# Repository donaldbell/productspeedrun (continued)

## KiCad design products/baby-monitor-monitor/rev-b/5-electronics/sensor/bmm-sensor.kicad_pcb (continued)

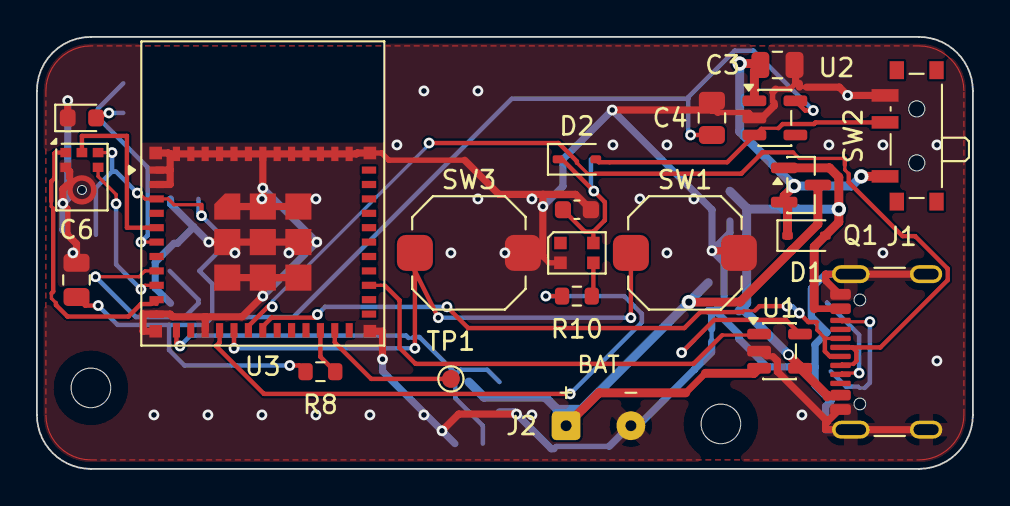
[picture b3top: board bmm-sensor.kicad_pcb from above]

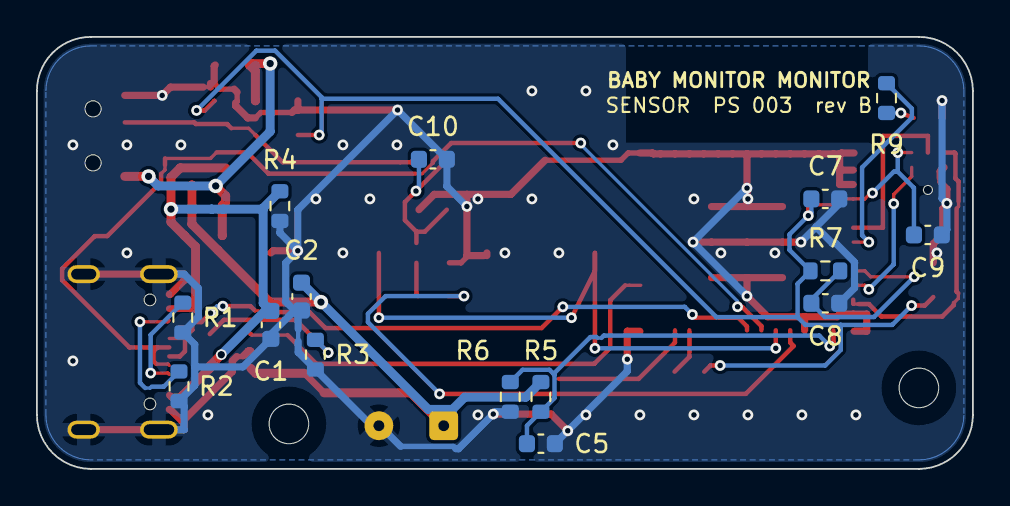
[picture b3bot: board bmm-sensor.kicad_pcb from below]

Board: 2 copper layers, 52.0 x 24.0 mm, 38 parts (15 on the bottom side), 25 nets.

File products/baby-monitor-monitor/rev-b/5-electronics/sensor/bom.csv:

Ref,Qty,Value,Description,Footprint,MPN
C1 C2,2,4.7uF,"Capacitor, ceramic, 4.7 uF 16 V X5R 0603",C_0603_1608Metric,CL10A475KO8NNNC
C3 C4 C6,3,10uF,"Capacitor, ceramic, 10 uF 25 V X5R 0805",C_0805_2012Metric,CL21A106KAYNNNE
C5 C7 C9 C11,4,100nF,"Capacitor, ceramic, 100 nF 50 V X7R 0603",C_0603_1608Metric,CC0603KRX7R9BB104
C8 C10,2,1uF,"Capacitor, ceramic, 1 uF 50 V X5R 0603",C_0603_1608Metric,CL10A105KB8NNNC
D1 D2,2,1N5819WS,Schottky 40 V 1 A SOD-323: USB into the system rail,D_SOD-323,1N5819WS
J1,1,USB-C,"USB-C receptacle, USB 2.0, 16 pin, top mount: power, charging and flashing (ESP32-C6 native USB)",USB_C_Receptacle_GCT_USB4105-xx-A_16P_TopMnt_Horizontal,USB4105-GF-A
LED1,1,green,LED green 0603: status under the front light pipe,LED_0603_1608Metric,KT-0603G
LED2,1,WS2812B-2020,RGB LED 2 x 2 mm under the clear snooze bar: location in the dark + state,LED_WS2812B-2020_PLCC4_2.0x2.0mm,WS2812B-2020
Q1,1,AO3401A,P-MOSFET -30 V -4 A SOT-23: battery into the system rail when USB is absent,SOT-23,AO3401A
R1 R2,2,5.1k,"Resistor, 1 %, 0603, 5.1k",R_0603_1608Metric,0603WAF5101T5E
R3,1,3.9k,"Resistor, 1 %, 0603, 3.9k",R_0603_1608Metric,0603WAF3901T5E
R4,1,100k,"Resistor, 1 %, 0603, 100k",R_0603_1608Metric,0603WAF1003T5E
R5 R6,2,1M,"Resistor, 1 %, 0603, 1M",R_0603_1608Metric,0603WAF1004T5E
R7 R8,2,10k,"Resistor, 1 %, 0603, 10k",R_0603_1608Metric,0603WAF1002T5E
R9,1,1k,"Resistor, 1 %, 0603, 1k",R_0603_1608Metric,0603WAF1001T5E
R10,1,100,"Resistor, 1 %, 0603, 100",R_0603_1608Metric,0603WAF1000T5E
SW1 SW3,2,I'M AWAKE,"Tact switch 6 x 6 x 5 mm SMD under the snooze bar's back end: tap = I'm awake, hold = test / pair",SW_Push_1TS009xxxx-xxxx-xxxx_6x6x5mm,1TS009A-1800-5000-CT
SW2,1,POWER,"Slide switch SPDT right-angle SMD (C&K PCM12): on = LDO enabled, off = EN to GND",SW_SPDT_PCM12,PCM12SMTR
U1,1,MCP73831T-2ACI/OT,"Li-ion/LiPo linear charger 4.2 V, SOT-23-5",SOT-23-5,MCP73831T-2ACI/OT
U2,1,AP2112K-3.3TRG1,"LDO 3.3 V 600 mA, SOT-23-5, enabled by the power switch",SOT-23-5,AP2112K-3.3TRG1
U3,1,ESP32-C6-MINI-1-N4,"ESP32-C6 Wi-Fi 6 / BLE 5 / 802.15.4 module (ESP-NOW), 4 MB flash, PCB antenna, 13.2 x 16.6 x 2.4 mm",ESP32-C6-MINI-1,ESP32-C6-MINI-1-N4
U4,1,ICS-43434,"I2S MEMS microphone, bottom port over a 1 mm hole through the board, L/R low = left slot",InvenSense_ICS-43434-6_3.5x2.65mm,ICS-43434
BT1,1,LiPo 2000 mAh,"LiPo 3.7 V ~2000 mAh with protection PCB, 103450 (10 x 34 x 50 mm), leads soldered to J2",off-board,generic 103450

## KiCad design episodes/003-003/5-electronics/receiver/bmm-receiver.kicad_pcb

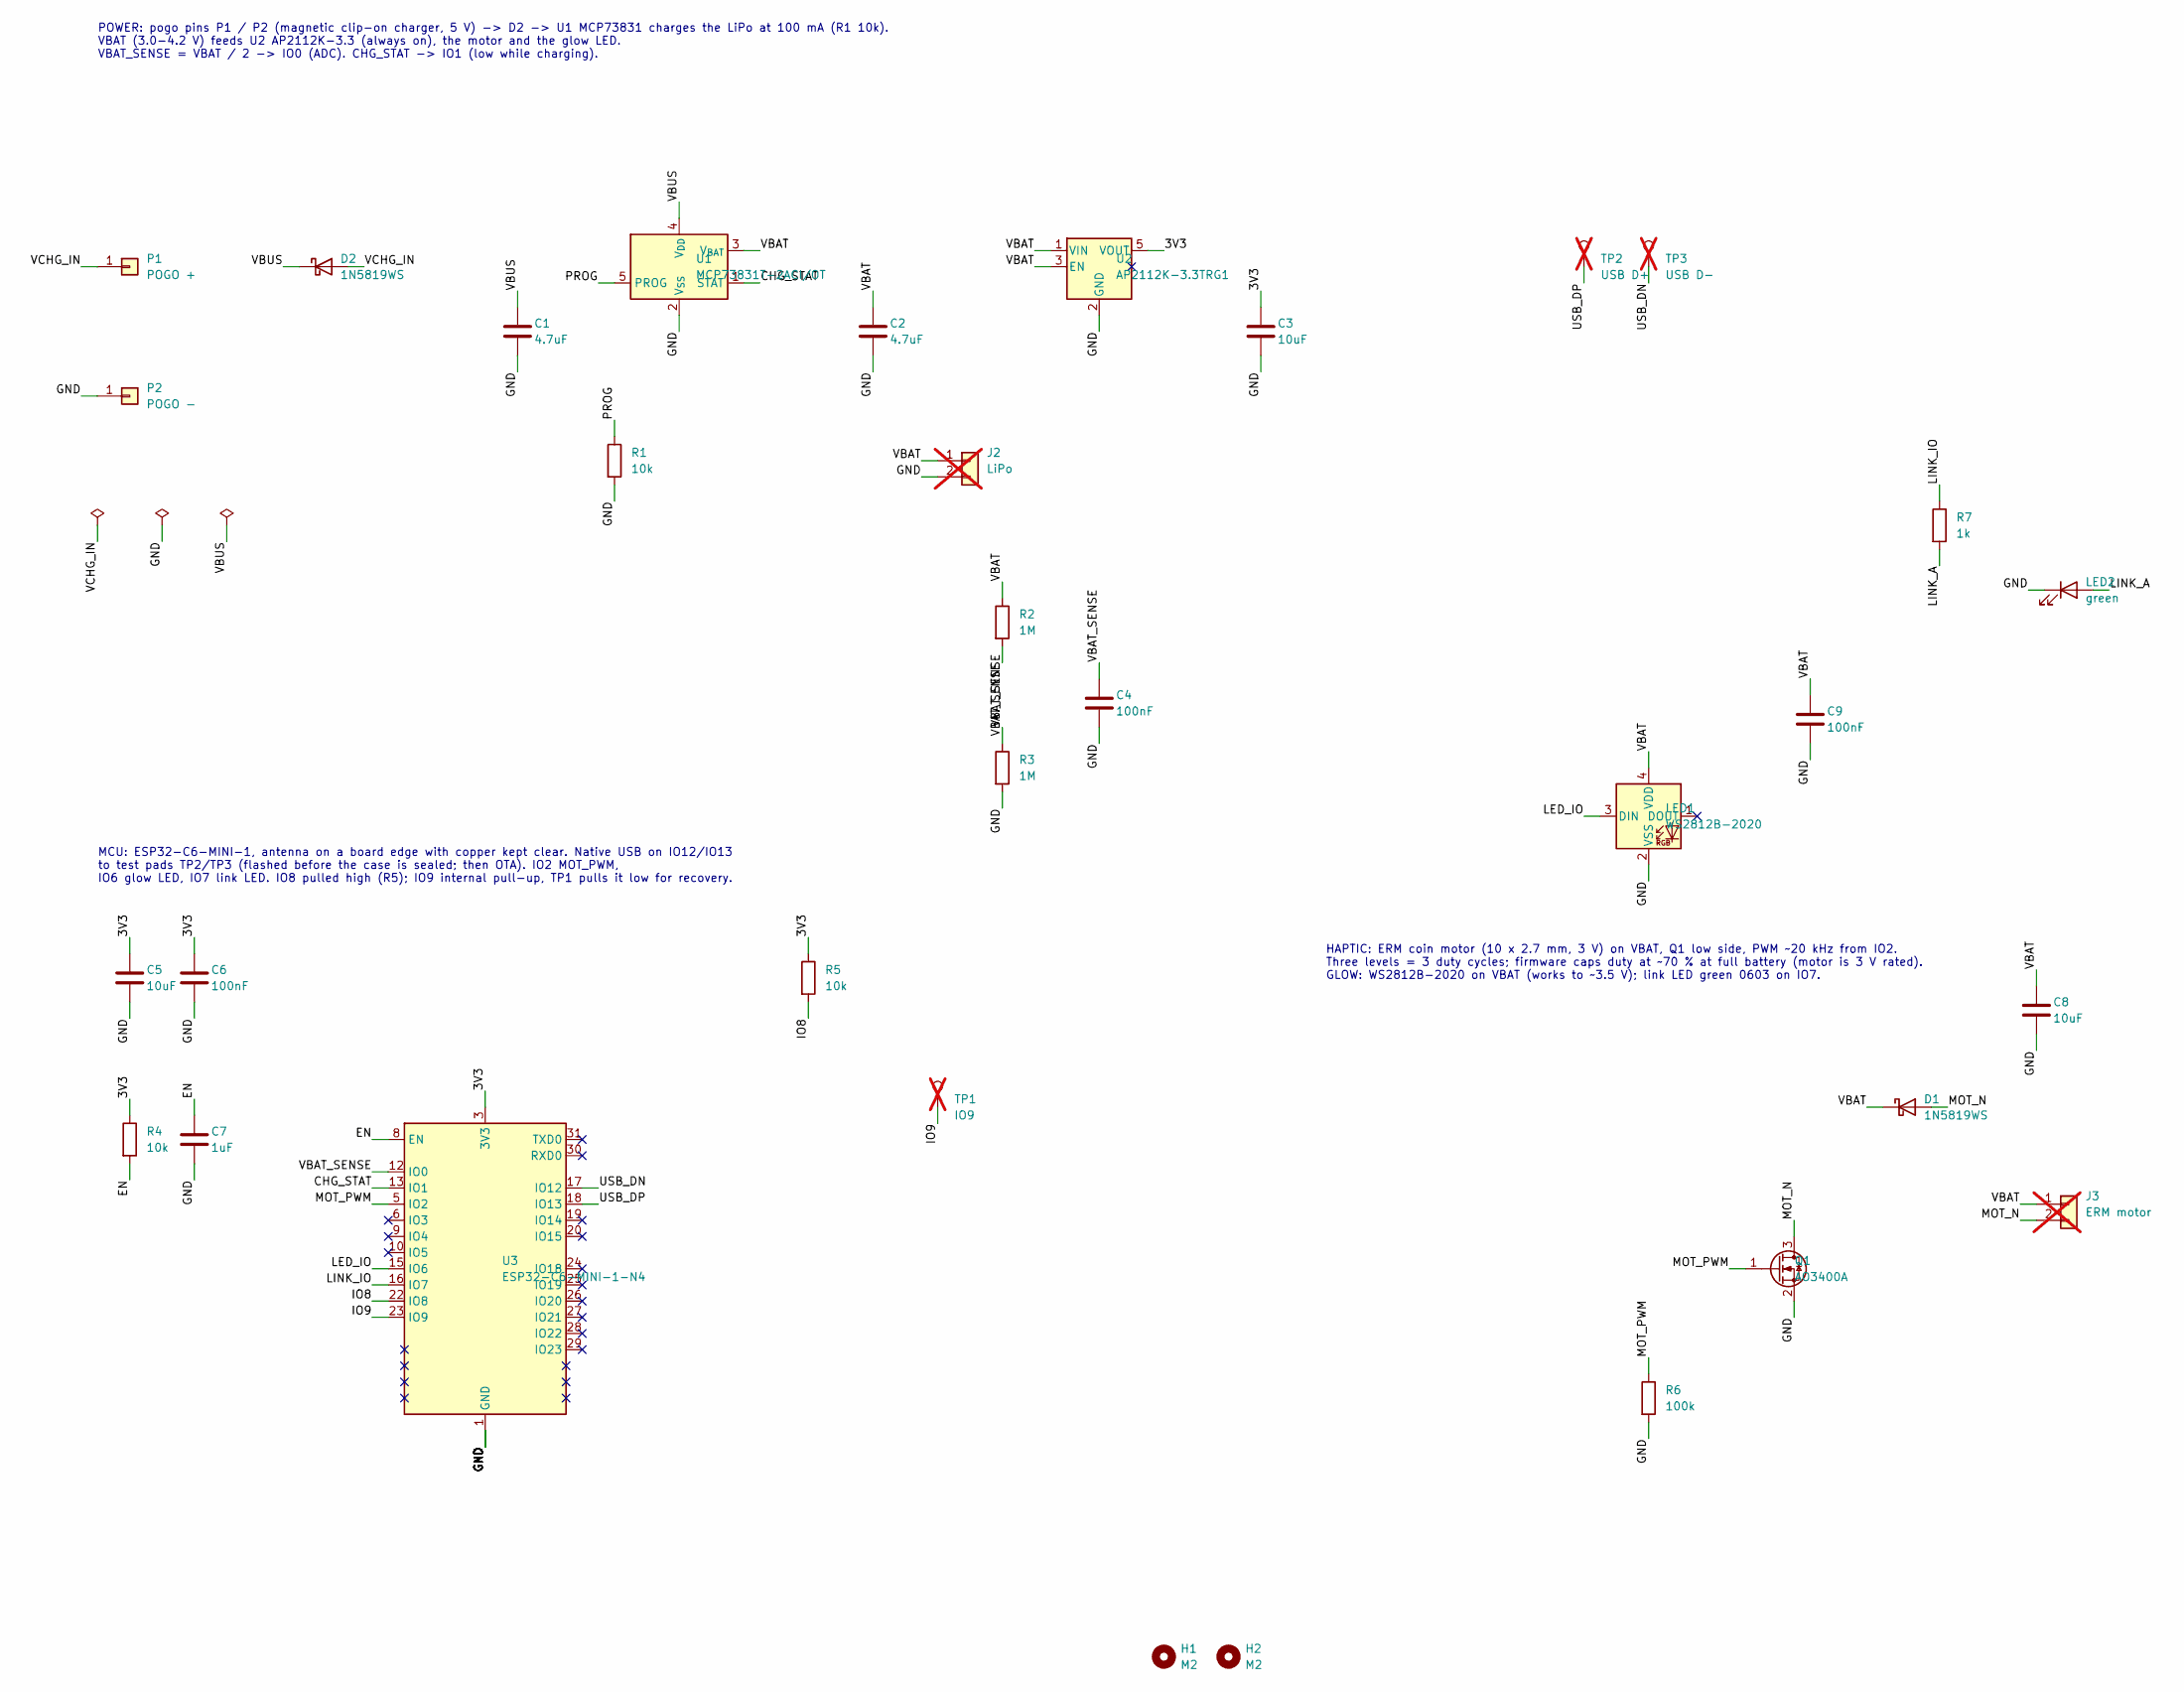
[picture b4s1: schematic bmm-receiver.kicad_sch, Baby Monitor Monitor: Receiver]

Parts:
C1, C2: 4.7uF; C_0603_1608Metric; MPN CL10A475KO8NNNC; LCSC C19666
C3, C5, C8: 10uF; C_0805_2012Metric; MPN CL21A106KAYNNNE; LCSC C15850
C4, C6, C9: 100nF; C_0603_1608Metric; MPN CC0603KRX7R9BB104; LCSC C14663
C7: 1uF; C_0603_1608Metric; MPN CL10A105KB8NNNC; LCSC C15849
D1, D2: 1N5819WS; D_SOD-323; MPN 1N5819WS; LCSC C191023
H1, H2: M2; MountingHole_2.2mm_M2
J2: LiPo; SolderWire-0.1sqmm_1x02_P3.6mm_D0.4mm_OD1mm; not fitted
J3: ERM motor; SolderWire-0.1sqmm_1x02_P3.6mm_D0.4mm_OD1mm; not fitted
LED1: WS2812B-2020; LED_WS2812B-2020_PLCC4_2.0x2.0mm; MPN WS2812B-2020; LCSC C965555
LED2: green; LED_0603_1608Metric; MPN KT-0603G; LCSC C72043
P1: POGO +; TestPoint_Pad_D2.0mm; MPN Mill-Max 0907 SMD spring pin (~5 mm)
P2: POGO -; TestPoint_Pad_D2.0mm; MPN Mill-Max 0907 SMD spring pin (~5 mm)
Q1: AO3400A; SOT-23; MPN AO3400A; LCSC C20917
R1, R4, R5: 10k; R_0603_1608Metric; MPN 0603WAF1002T5E; LCSC C25804
R2, R3: 1M; R_0603_1608Metric; MPN 0603WAF1004T5E; LCSC C22935
R6: 100k; R_0603_1608Metric; MPN 0603WAF1003T5E; LCSC C25803
R7: 1k; R_0603_1608Metric; MPN 0603WAF1001T5E; LCSC C21190
TP1: IO9; TestPoint_Pad_D1.0mm; not fitted
TP2: USB D+; TestPoint_Pad_D1.0mm; not fitted
TP3: USB D-; TestPoint_Pad_D1.0mm; not fitted
U1: MCP73831T-2ACI/OT; SOT-23-5; MPN MCP73831T-2ACI/OT; LCSC C424093
U2: AP2112K-3.3TRG1; SOT-23-5; MPN AP2112K-3.3TRG1; LCSC C51118
U3: ESP32-C6-MINI-1-N4; ESP32-C6-MINI-1; MPN ESP32-C6-MINI-1-N4

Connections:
/3V3: C3.1, C5.1, C6.1, R4.1, R5.1, U2.5 (VOUT), U3.3 (3V3)
/CHG_STAT: U1.1 (STAT), U3.13 (IO1)
/EN: C7.1, R4.2, U3.8 (EN)
/GND: C1.2, C2.2, C3.2, C4.2, C5.2, C6.2, C7.2, C8.2, C9.2, J2.2, LED1.2 (VSS), LED2.1 (K), P2.1, Q1.2 (S), R1.2, R3.2, R6.2, U1.2 (V_{SS}), U2.2 (GND), U3.1 (GND), U3.2 (GND), U3.11 (GND), U3.14 (GND), U3.36 (GND), U3.37 (GND), U3.38 (GND), U3.39 (GND), U3.40 (GND), U3.41 (GND), U3.42 (GND), U3.43 (GND), U3.44 (GND), U3.45 (GND), U3.46 (GND), U3.47 (GND), U3.48 (GND), U3.49 (GND), U3.50 (GND), U3.51 (GND), U3.52 (GND), U3.53 (GND)
/IO8: R5.2, U3.22 (IO8)
/IO9: TP1.1, U3.23 (IO9)
/LED_IO: LED1.3 (DIN), U3.15 (IO6)
/LINK_A: LED2.2 (A), R7.2
/LINK_IO: R7.1, U3.16 (IO7)
/MOT_N: D1.2 (A), J3.2, Q1.3 (D)
/MOT_PWM: Q1.1 (G), R6.1, U3.5 (IO2)
/PROG: R1.1, U1.5 (PROG)
/USB_DN: TP3.1, U3.17 (IO12)
/USB_DP: TP2.1, U3.18 (IO13)
/VBAT: C2.1, C8.1, C9.1, D1.1 (K), J2.1, J3.1, LED1.4 (VDD), R2.1, U1.3 (V_{BAT}), U2.1 (VIN), U2.3 (EN)
/VBAT_SENSE: C4.1, R2.2, R3.1, U3.12 (IO0)
/VBUS: C1.1, D2.1 (K), U1.4 (V_{DD})
/VCHG_IN: D2.2 (A), P1.1

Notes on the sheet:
POWER: pogo pins P1 / P2 (magnetic clip-on charger, 5 V) -> D2 -> U1 MCP73831 charges the LiPo at 100 mA (R1 10k). VBAT (3.0-4.2 V) feeds U2 AP2112K-3.3 (always on), the motor and the glow LED. VBAT_SENSE = VBAT / 2 -> IO0 (ADC). CHG_STAT -> IO1 (low while charging).
MCU: ESP32-C6-MINI-1, antenna on a board edge with copper kept clear. Native USB on IO12/IO13 to test pads TP2/TP3 (flashed before the case is sealed; then OTA). IO2 MOT_PWM, IO6 glow LED, IO7 link LED. IO8 pulled high (R5); IO9 internal pull-up, TP1 pulls it low for recovery.
HAPTIC: ERM coin motor (10 x 2.7 mm, 3 V) on VBAT, Q1 low side, PWM ~20 kHz from IO2. Three levels = 3 duty cycles; firmware caps duty at ~70 % at full battery (motor is 3 V rated). GLOW: WS2812B-2020 on VBAT (works to ~3.5 V); link LED green 0603 on IO7.

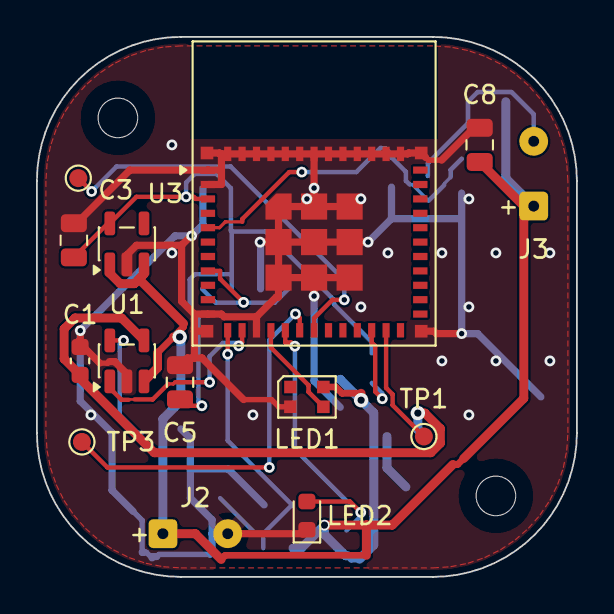
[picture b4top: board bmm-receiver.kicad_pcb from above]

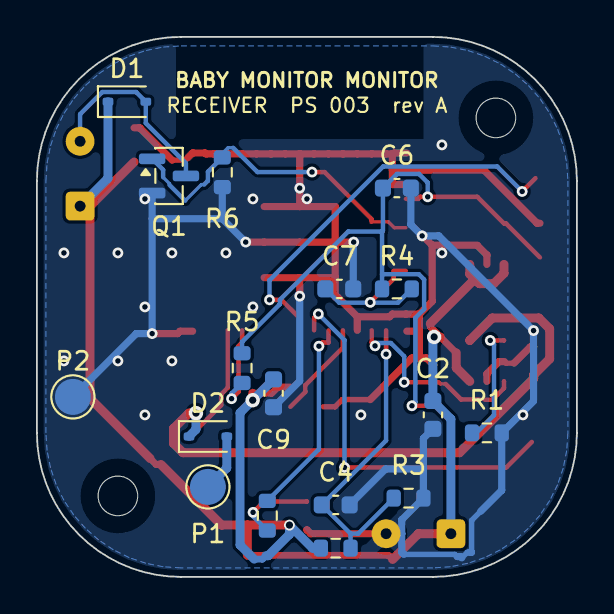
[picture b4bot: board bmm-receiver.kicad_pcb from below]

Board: 2 copper layers, 30.0 x 30.0 mm, 33 parts (17 on the bottom side), 18 nets.

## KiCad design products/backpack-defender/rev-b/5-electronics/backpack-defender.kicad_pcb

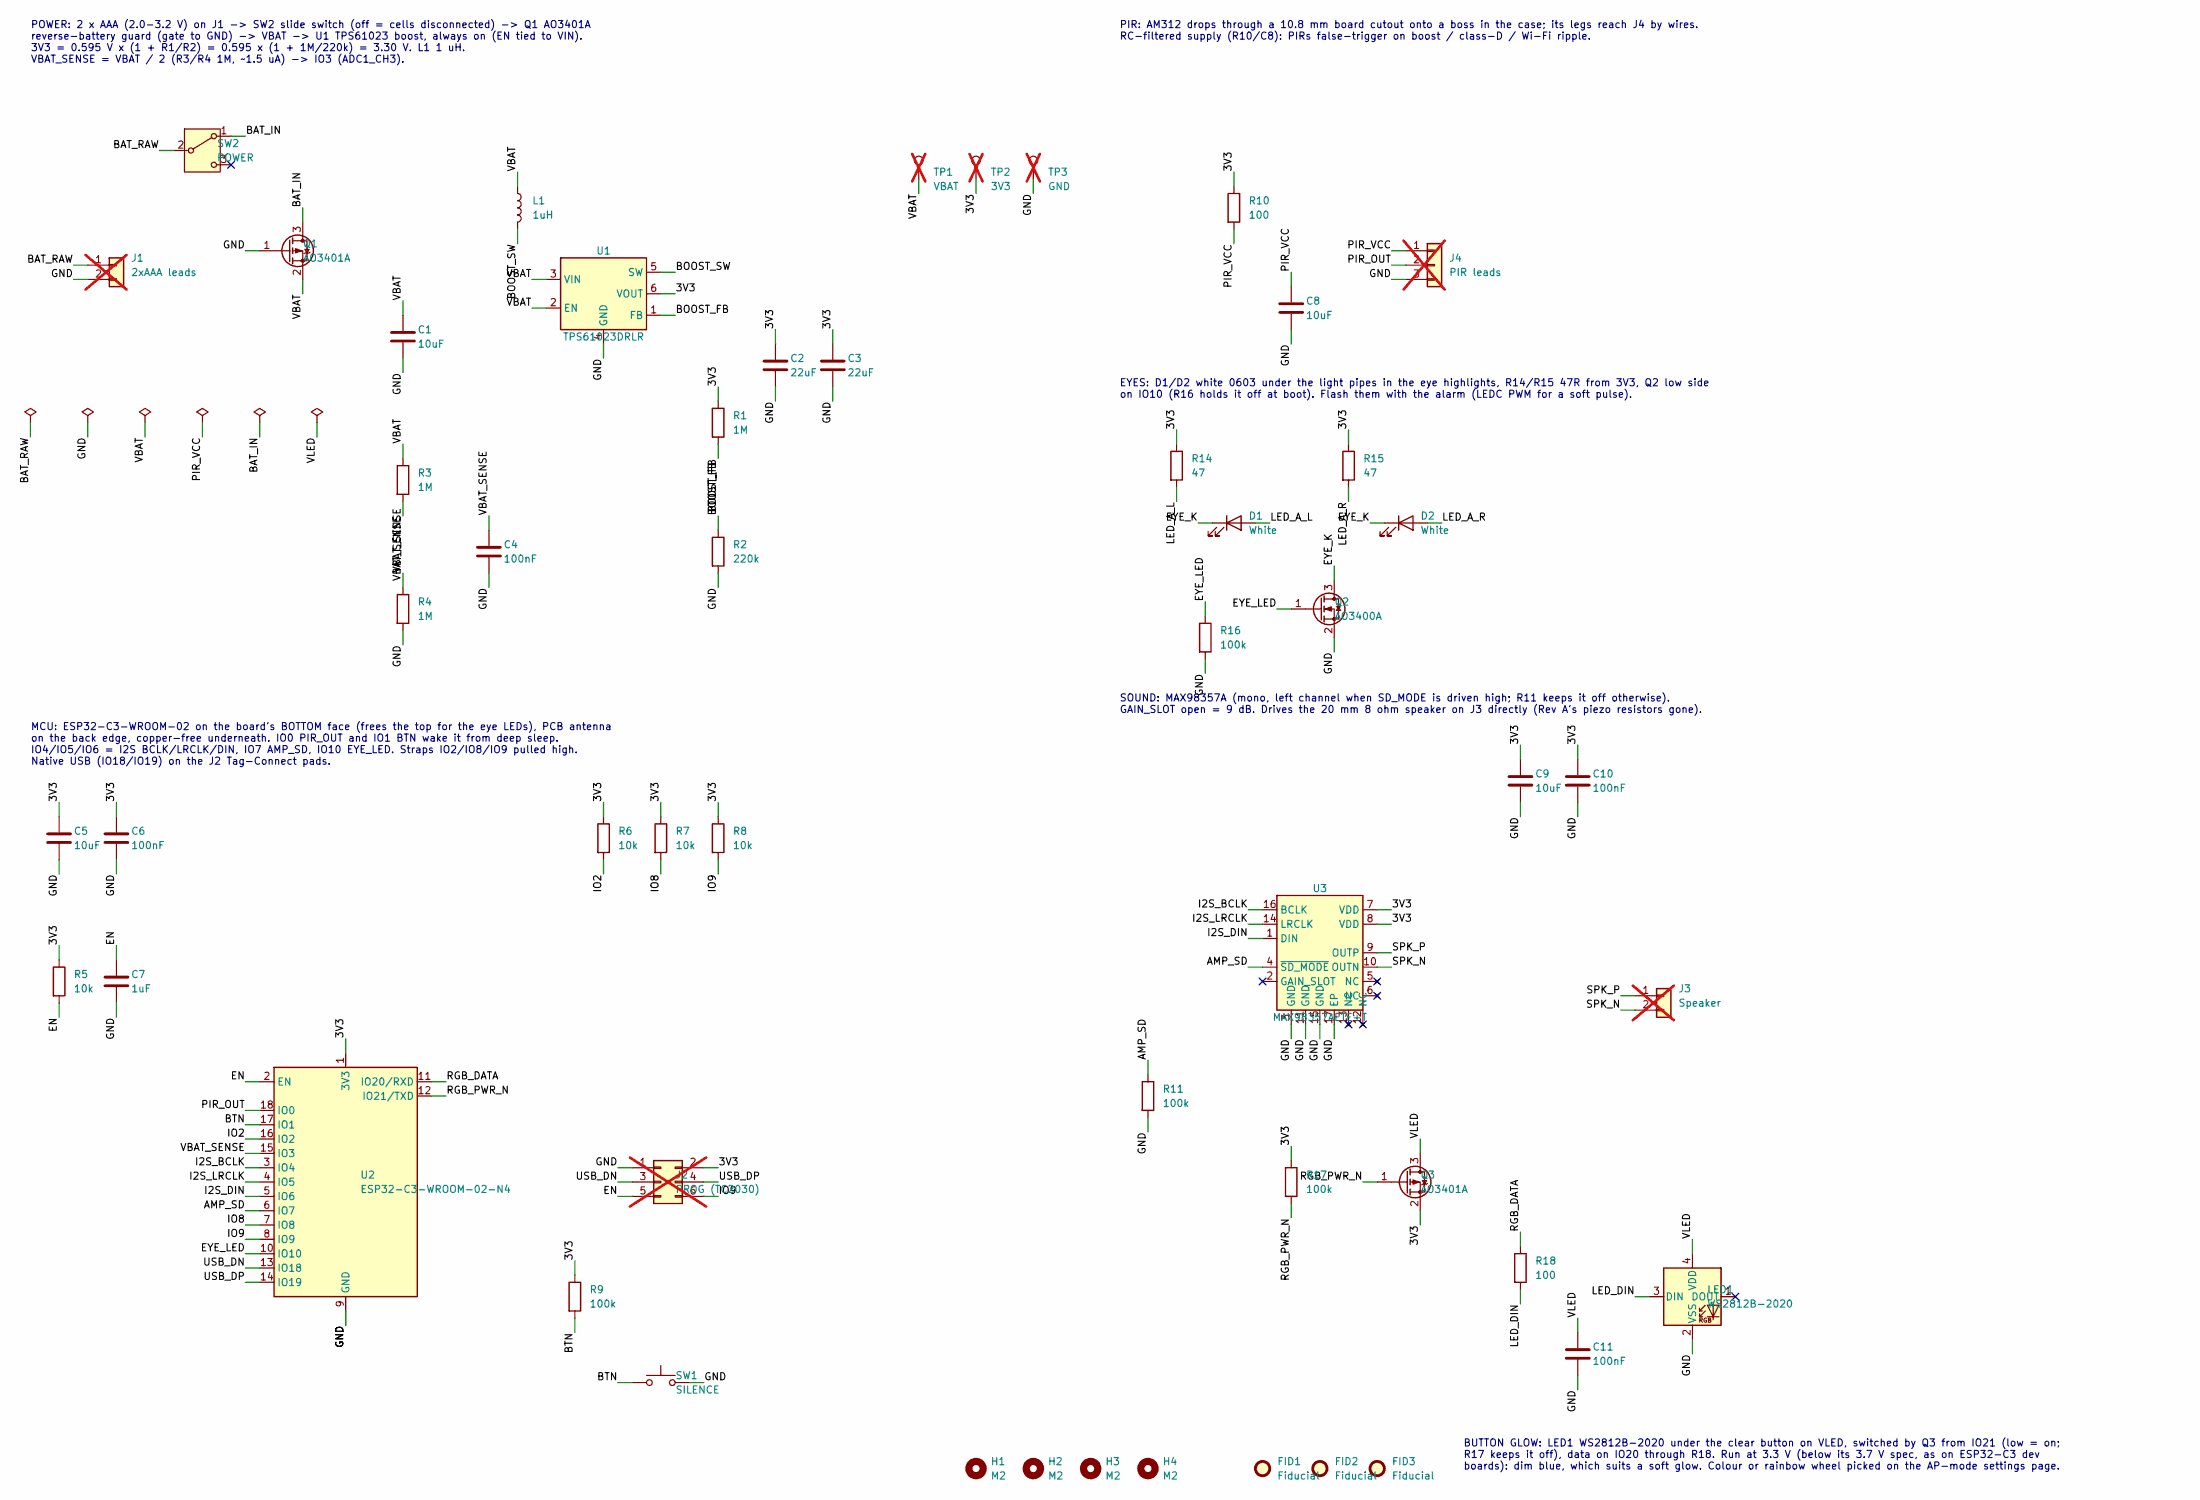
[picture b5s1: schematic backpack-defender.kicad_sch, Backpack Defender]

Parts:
C1, C5, C8, C9: 10uF; C_0805_2012Metric; MPN CL21A106KAYNNNE; LCSC C15850
C2, C3: 22uF; C_0805_2012Metric; MPN CL21A226MAQNNNE; LCSC C45783
C4, C6, C10, C11: 100nF; C_0603_1608Metric; MPN CC0603KRX7R9BB104; LCSC C14663
C7: 1uF; C_0603_1608Metric; MPN CL10A105KB8NNNC; LCSC C15849
D1, D2: White; LED_0603_1608Metric; MPN KT-0603W; LCSC C2290
FID1, FID2, FID3: Fiducial; Fiducial_1mm_Mask2mm
H1, H2, H3, H4: M2; MountingHole_2.2mm_M2
J1: 2xAAA leads; SolderWire-0.25sqmm_1x02_P4.2mm_D0.65mm_OD1.7mm; not fitted
J2: PROG (TC2030); Tag-Connect_TC2030-IDC-NL_2x03_P1.27mm_Vertical; MPN TC2030-IDC-NL (cable); not fitted
J3: Speaker; SolderWire-0.25sqmm_1x02_P4.2mm_D0.65mm_OD1.7mm; not fitted
J4: PIR leads; SolderWire-0.25sqmm_1x03_P4.2mm_D0.65mm_OD1.7mm; not fitted
L1: 1uH; L_Changjiang_FXL0624; MPN FXL0624-1R0-M; LCSC C524602
LED1: WS2812B-2020; LED_WS2812B-2020_PLCC4_2.0x2.0mm; MPN WS2812B-2020; LCSC C965555
Q1, Q3: AO3401A; SOT-23; MPN AO3401A; LCSC C15127
Q2: AO3400A; SOT-23; MPN AO3400A; LCSC C20917
R1, R3, R4: 1M; R_0603_1608Metric; MPN 0603WAF1004T5E; LCSC C22935
R2: 220k; R_0603_1608Metric; MPN 0603WAF2203T5E
R5, R6, R7, R8: 10k; R_0603_1608Metric; MPN 0603WAF1002T5E; LCSC C25804
R9, R11, R16, R17: 100k; R_0603_1608Metric; MPN 0603WAF1003T5E; LCSC C25803
R10, R18: 100; R_0603_1608Metric; MPN 0603WAF1000T5E; LCSC C22775
R14, R15: 47; R_0603_1608Metric; MPN 0603WAF470JT5E; LCSC C23182
SW1: SILENCE; SW_PUSH-12mm; MPN TS-1212-4.3 (12x12x4.3 THT)
SW2: POWER; SW_Slide_SPDT_Angled_CK_OS102011MA1Q; MPN OS102011MA1QN1
TP1: VBAT; TestPoint_Pad_D1.5mm; not fitted
TP2: 3V3; TestPoint_Pad_D1.5mm; not fitted
TP3: GND; TestPoint_Pad_D1.5mm; not fitted
U1: TPS61023DRLR; SOT-563; MPN TPS61023DRLR; LCSC C919459
U2: ESP32-C3-WROOM-02-N4; ESP32-C3-WROOM-02; MPN ESP32-C3-WROOM-02-N4; LCSC C2934560
U3: MAX98357AETE+T; TQFN-16-1EP_3x3mm_P0.5mm_EP1.23x1.23mm_ThermalVias; MPN MAX98357AETE+T

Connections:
/3V3: C2.1, C3.1, C5.1, C6.1, C9.1, C10.1, J2.2, Q3.2 (S), R1.1, R5.1, R6.1, R7.1, R8.1, R9.1, R10.1, R14.1, R15.1, R17.1, TP2.1, U1.6 (VOUT), U2.1 (3V3), U3.7 (VDD), U3.8 (VDD)
/AMP_SD: R11.1, U2.6 (IO7), U3.4 (~SD_MODE)
/BAT_IN: Q1.3 (D), SW2.1 (A)
/BAT_RAW: J1.1, SW2.2 (B)
/BOOST_FB: R1.2, R2.1, U1.1 (FB)
/BOOST_SW: L1.2, U1.5 (SW)
/BTN: R9.2, SW1.1, U2.17 (IO1)
/EN: C7.1, J2.5, R5.2, U2.2 (EN)
/EYE_K: D1.1 (K), D2.1 (K), Q2.3 (D)
/EYE_LED: Q2.1 (G), R16.1, U2.10 (IO10)
/GND: C1.2, C2.2, C3.2, C4.2, C5.2, C6.2, C7.2, C8.2, C9.2, C10.2, C11.2, J1.2, J2.1, J4.3, LED1.2 (VSS), Q1.1 (G), Q2.2 (S), R2.2, R4.2, R11.2, R16.2, SW1.2, TP3.1, U1.4 (GND), U2.9 (GND), U2.19 (GND), U3.3 (GND), U3.11 (GND), U3.15 (GND), U3.17 (EP)
/I2S_BCLK: U2.3 (IO4), U3.16 (BCLK)
/I2S_DIN: U2.5 (IO6), U3.1 (DIN)
/I2S_LRCLK: U2.4 (IO5), U3.14 (LRCLK)
/IO2: R6.2, U2.16 (IO2)
/IO8: R7.2, U2.7 (IO8)
/IO9: J2.6, R8.2, U2.8 (IO9)
/LED_A_L: D1.2 (A), R14.2
/LED_A_R: D2.2 (A), R15.2
/LED_DIN: LED1.3 (DIN), R18.2
/PIR_OUT: J4.2, U2.18 (IO0)
/PIR_VCC: C8.1, J4.1, R10.2
/RGB_DATA: R18.1, U2.11 (IO20/RXD)
/RGB_PWR_N: Q3.1 (G), R17.2, U2.12 (IO21/TXD)
/SPK_N: J3.2, U3.10 (OUTN)
/SPK_P: J3.1, U3.9 (OUTP)
/USB_DN: J2.3, U2.13 (IO18)
/USB_DP: J2.4, U2.14 (IO19)
/VBAT: C1.1, L1.1, Q1.2 (S), R3.1, TP1.1, U1.2 (EN), U1.3 (VIN)
/VBAT_SENSE: C4.1, R3.2, R4.1, U2.15 (IO3)
/VLED: C11.1, LED1.4 (VDD), Q3.3 (D)

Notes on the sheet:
POWER: 2 x AAA (2.0-3.2 V) on J1 -> SW2 slide switch (off = cells disconnected) -> Q1 AO3401A reverse-battery guard (gate to GND) -> VBAT -> U1 TPS61023 boost, always on (EN tied to VIN). 3V3 = 0.595 V x (1 + R1/R2) = 0.595 x (1 + 1M/220k) = 3.30 V. L1 1 uH. VBAT_SENSE = VBAT / 2 (R3/R4 1M, ~1.5 uA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
MCU: ESP32-C3-WROOM-02 on the board's BOTTOM face (frees the top for the eye LEDs), PCB antenna on the back edge, copper-free underneath. IO0 PIR_OUT and IO1 BTN wake it from deep sleep. IO4/IO5/IO6 = I2S BCLK/LRCLK/DIN, IO7 AMP_SD, IO10 EYE_LED. Straps IO2/IO8/IO9 pulled high. Native USB (IO18/IO1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
PIR: AM312 drops through a 10.8 mm board cutout onto a boss in the case; its legs reach J4 by wires. RC-filtered supply (R10/C8): PIRs false-trigger on boost / class-D / Wi-Fi ripple.
EYES: D1/D2 white 0603 under the light pipes in the eye highlights, R14/R15 47R from 3V3, Q2 low side on IO10 (R16 holds it off at boot). Flash them with the alarm (LEDC PWM for a soft pulse).
BUTTON GLOW: LED1 WS2812B-2020 under the clear button on VLED, switched by Q3 from IO21 (low = on; R17 keeps it off), data on IO20 through R18. Run at 3.3 V (below its 3.7 V spec, as on ESP32-C3 dev boards): dim blue, which suits a soft glow. Colour or rainbow wheel picked on the AP-mode settings p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
SOUND: MAX98357A (mono, left channel when SD_MODE is driven high; R11 keeps it off otherwise). GAIN_SLOT open = 9 dB. Drives the 20 mm 8 ohm speaker on J3 directly (Rev A's piezo resistors gone).

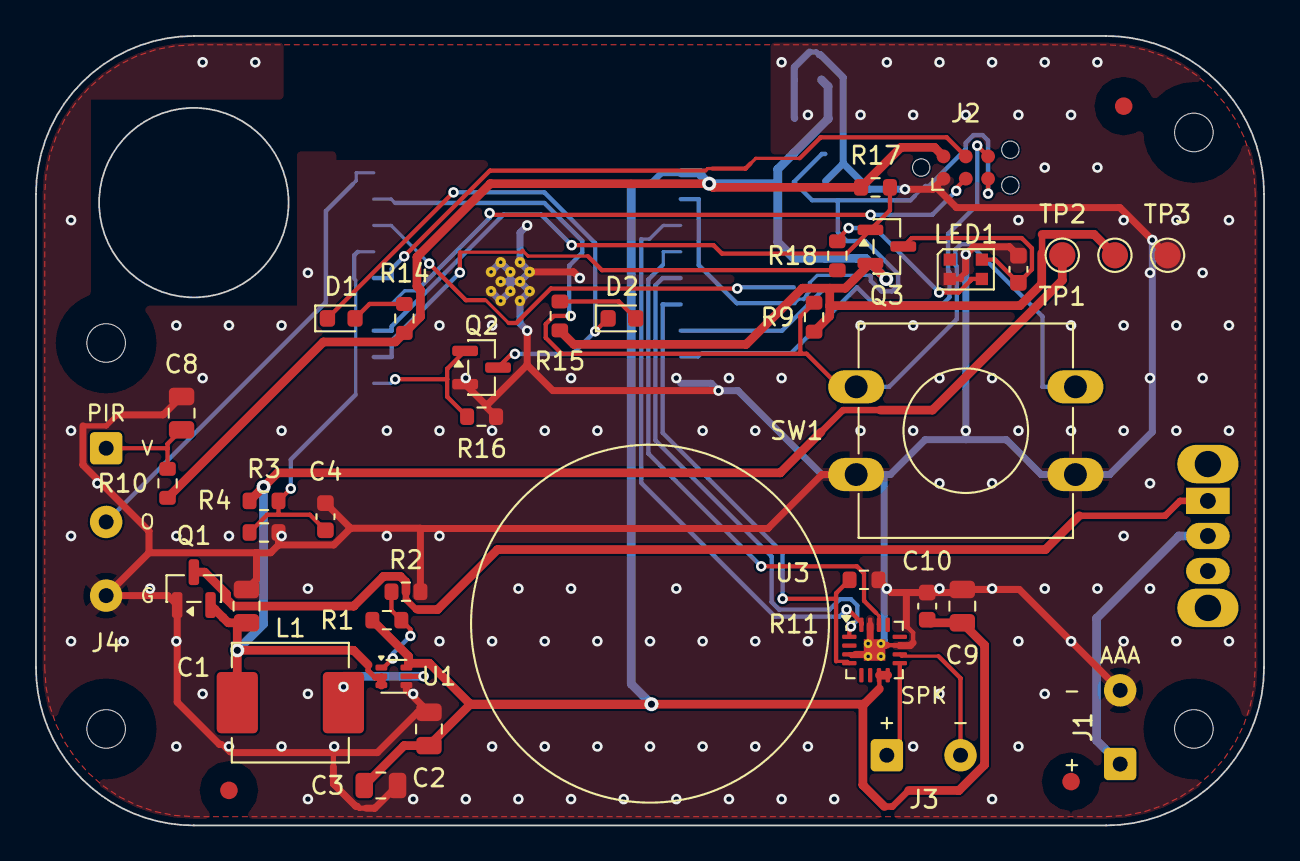
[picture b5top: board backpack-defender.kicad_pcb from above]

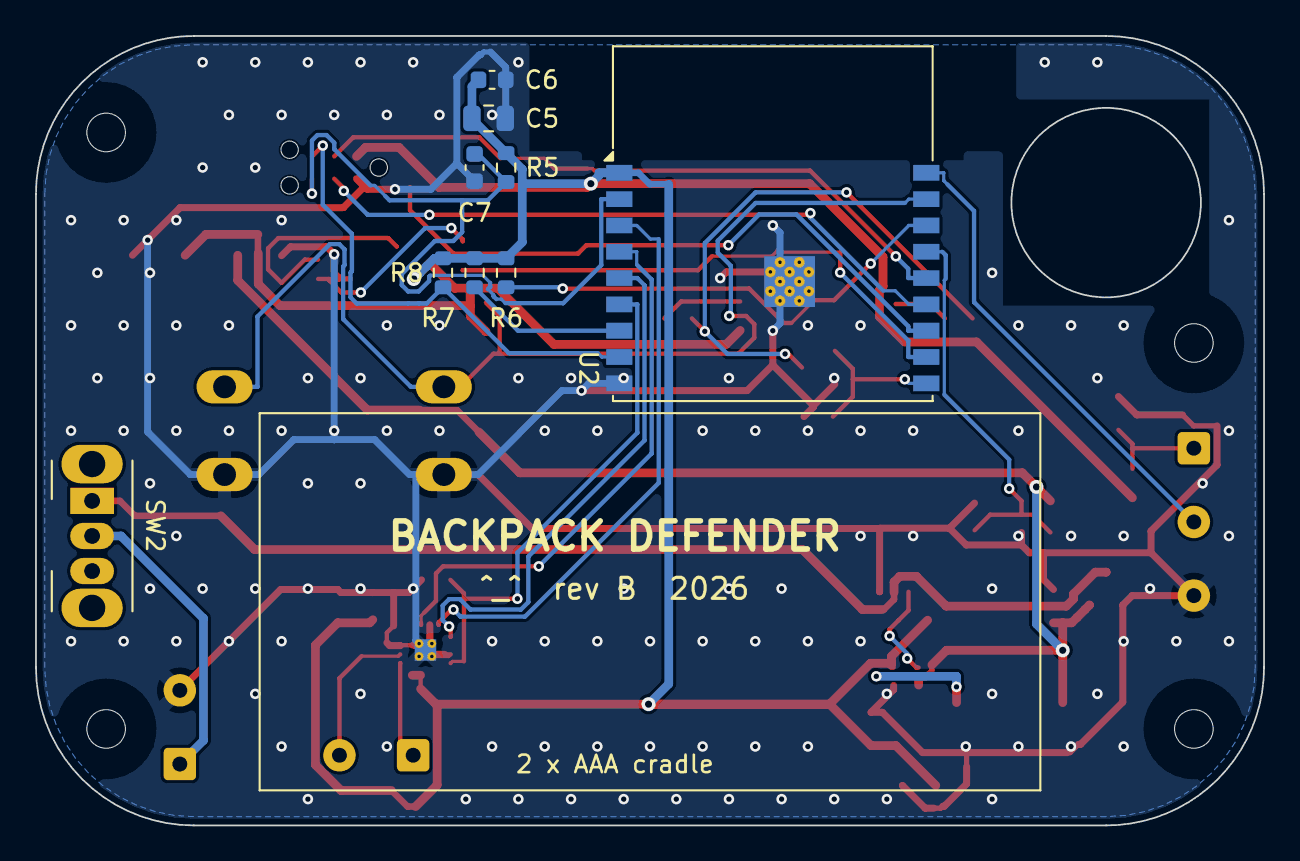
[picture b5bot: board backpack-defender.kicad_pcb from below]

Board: 2 copper layers, 70.0 x 45.0 mm, 53 parts (9 on the bottom side), 31 nets.

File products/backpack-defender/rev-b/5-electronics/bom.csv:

Ref,Qty,Value,Description,Footprint,MPN
C1 C5 C8 C9,4,10uF,"Capacitor, ceramic, 10 uF 25 V X5R 0805",C_0805_2012Metric,CL21A106KAYNNNE
C2 C3,2,22uF,"Capacitor, ceramic, 22 uF 25 V X5R 0805",C_0805_2012Metric,CL21A226MAQNNNE
C4 C6 C10 C11,4,100nF,"Capacitor, ceramic, 100 nF 50 V X7R 0603",C_0603_1608Metric,CC0603KRX7R9BB104
C7,1,1uF,"Capacitor, ceramic, 1 uF 50 V X5R 0603",C_0603_1608Metric,CL10A105KB8NNNC
D1 D2,2,White,"LED white 0603, under the left eye's light pipe",LED_0603_1608Metric,KT-0603W
L1,1,1uH,"Inductor, power, 1 uH, 9 A sat, 7 x 6.6 mm",L_Changjiang_FXL0624,FXL0624-1R0-M
LED1,1,WS2812B-2020,"RGB LED 2 x 2 mm, addressable, under the clear button",LED_WS2812B-2020_PLCC4_2.0x2.0mm,WS2812B-2020
Q1 Q3,2,AO3401A,"P-MOSFET -30 V -4 A SOT-23: reverse-battery guard, drain to the cells, gate to GND",SOT-23,AO3401A
Q2,1,AO3400A,N-MOSFET 30 V 5.7 A SOT-23: switches both eye LEDs from IO10,SOT-23,AO3400A
R1 R3 R4,3,1M,"Resistor, 1 %, 0603, 1M",R_0603_1608Metric,0603WAF1004T5E
R2,1,220k,"Resistor, 1 %, 0603, 220k",R_0603_1608Metric,0603WAF2203T5E
R5 R6 R7 R8,4,10k,"Resistor, 1 %, 0603, 10k",R_0603_1608Metric,0603WAF1002T5E
R9 R11 R16 R17,4,100k,"Resistor, 1 %, 0603, 100k",R_0603_1608Metric,0603WAF1003T5E
R10 R18,2,100,"Resistor, 1 %, 0603, 100",R_0603_1608Metric,0603WAF1000T5E
R14 R15,2,47,"Resistor, 1 %, 0603, 47",R_0603_1608Metric,0603WAF470JT5E
SW1,1,SILENCE,"Tactile switch 12 x 12 x 4.3 mm THT (low profile), under the big silence button",SW_PUSH-12mm,TS-1212-4.3 (12x12x4.3 THT)
SW2,1,POWER,"Slide switch SPDT right-angle THT, 4 mm lever out through the case's right end: disconnects the cells",SW_Slide_SPDT_Angled_CK_OS102011MA1Q,OS102011MA1QN1
U1,1,TPS61023DRLR,"Synchronous boost converter 0.5-5.5 V in, 3.7 A switch, SOT-563",SOT-563,TPS61023DRLR
U2,1,ESP32-C3-WROOM-02-N4,"ESP32-C3 Wi-Fi/BLE module, 4 MB flash, PCB antenna, 18 x 20 x 3.2 mm",ESP32-C3-WROOM-02,ESP32-C3-WROOM-02-N4
U3,1,MAX98357AETE+T,"I2S class-D mono amplifier, TQFN-16 3 x 3 mm",TQFN-16-1EP_3x3mm_P0.5mm_EP1.23x1.23mm_ThermalVias,MAX98357AETE+T
BT1,1,2xAAA cradle,"2 x AAA cells in a cradle in the bottom plate, spring contacts wired to J1",off-board,2 x Keystone-style AAA contact pairs
U4,1,AM312,"Mini PIR motion sensor, dome through the lid, wired to J4",off-board,AM312
LS1,1,Speaker 20 mm 8 ohm,"Micro speaker 20 x 4 mm, 8 ohm 1 W, faces the lid grille on a foam ring, wired to J3",off-board,generic 2004 micro speaker
